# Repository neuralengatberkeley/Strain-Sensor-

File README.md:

# Strain-Sensor-

# ABS Filmanent LM Channels:

3D printed ABS channels to be dissolved in acetone:  

CAD file for 3d prints shown in image above:  ...CAD Files/abs_lofted_insert/basic strain gauge 0p02.ipt

3D printer used -> Original Prusa MK4s

# Strain Sensor Fabrication Procedure:

#  Auto Bender:

All Structural parts (e.g. plates, shaft collars, fasteners) were purchased from goBILDA:  https://www.gobilda.com/

# AutoBender Sensor Circuit:

# AutoBender PCB (which inlcudes sensor circuit and servo circuit):

AutoBender PCB design can be found here in ...Fritzing Files/Voltage Divider PCB/bender PCB.fzz

# Interpreting CSV Data File Columns:

Column A:  Disregard.  It was initially meant to provide the theoretical bend angle, but it is wrong and not used in any calculation.

Column B:  Adafruit BNO055 IMU Pitch Euler Angle (degrees)

Column C:  ADC Value as read from Adafruit Sensor MCP3421 18-Bit ADC (The ADC sensor is in parrallel with the Liquid Metal Strain Gauge (LMSG).  The LMSG is in series 			with a 100 ohm resistor).  Since the code is set to read 14-bits, the possible range of values is from 0 to 2^14 - 1.

Column D:  ADC Value as read from Hall Effect Rotary Encoder (https://p3america.com/erc-series/?srsltid=AfmBOoqSsWeZSXtsMrmoHyB0DRfSCzyFlUfcnEff0gpcv0NyMvrGhVz7).  The 		rotary encoder can rotate from 0 to 320 degrees.  There is a mechanical stop at 0 and 320 degrees.  Since the rotary encoder is connected directly to 			Arduino Uno, the adc output from the Arduino can have values from 0 to 2^10 - 1.  

Note about converting rotary encoder adc value to angle in degrees:  

As a result of this calculation, the rotatry encoder angle should always start at 0 degrees.  The initial IMU angle in degrees typically starts around ~ 3 degrees.  

# Derivation of Change in Resistance Formula as a Function of Axial Strain:

If an axial load is applied to a solid in the x-direction, the solid's lateral dimensions in the y- and z-directions will typically contract, depending on the material properties. The ratio of lateral contraction (negative strain) to axial extension (positive strain) is called Poisson's ratio. The definition includes a negative sign, ensuring that Poisson's ratio is a positive value for materials that contract laterally when stretched axially. 

References:  

1. Soft Robotics Toolkit. (n.d.). Casting soft robots. Retrieved January 14, 2025, 
	from https://softroboticstoolkit.com/book/export/html/206021
2. Craig Jr., R. R. (2011). Mechanics of materials (3rd ed.). Wiley.
3. Hambley, A.R. (2011). Electrical Engineering Principles and Applications (5th ed.).  Prentice Hall.
4. Callister Jr., W. D., & Rethwisch, D. G.  Materials Science and Engineering: An Introduction (10th ed.).  Wiley.
5. Chen, J., Zhang, J., Luo, Z., Zhang, J., Li, L., Su, Y., Gao, X., Li, Y., Tang, W., Cao, C., Liu, Q., Wang, L., & Li, H. (2020). 
	Superelastic, sensitive, and low hysteresis flexible strain sensor based on wave-patterned liquid metal for 
	human activity monitoring. ACS Applied Materials & Interfaces, 12(19), 22200–22211. 
	https://doi.org/10.1021/acsami.0c04709

# Explanation of Model Developed for Axial Strain as a Function of Bend Angle:

The finger joints are modeled as a hinged joint where the leaf rotation axis is concentric with the knuckle axis.  Additionally, the interial surface of the leaf is in contact with the exterior surface of the knuckle.  The change in length of the sample is calculated from the arc length forumla. This model is presented in the image below:

However, in our autobender, the interior rotating surface of the leaf is offset from the exterior surface of the knuckle by an amount delta.  The adjusted AutoBender model is presented in the image below:  

# Expected Trend for Normalized Resistance vs Axial Strain:

The plot below shows theoretical curves of normalized resistance versus axial strain for samples with varying lengths L, but identical liquid metal channel length (Lo) and cross-sectional area (A). The following trends are observed:

1.  As sample length, L, increases (assuming same liquid metal channel lengths and cross-sectional area), the slope of the curve decreases.
2.  A longer sample will experience less axial strain at a 90 degree bend angle
3.  For axial strains below approximately 40% (e.g., in human knuckle models), the relationship can be approximated as linear.
4.  As bend radius (R in this case, not r as indicated in human knuckle model image :/) increases, axial strain also increases for the same bend angle. For example, a strain sensor on a larger knuckle would experience greater axial strain compared to one on a smaller knuckle.  

# "Gluing" LMSG on to fingers:

"paint" Derma-Tac (https://www.smooth-on.com/products/derma-tac/) AND Skin-Tite (https://www.smooth-on.com/products/skin-tite/) onto finger, place sensor on finger for a couple minutes until cross-linking occurs

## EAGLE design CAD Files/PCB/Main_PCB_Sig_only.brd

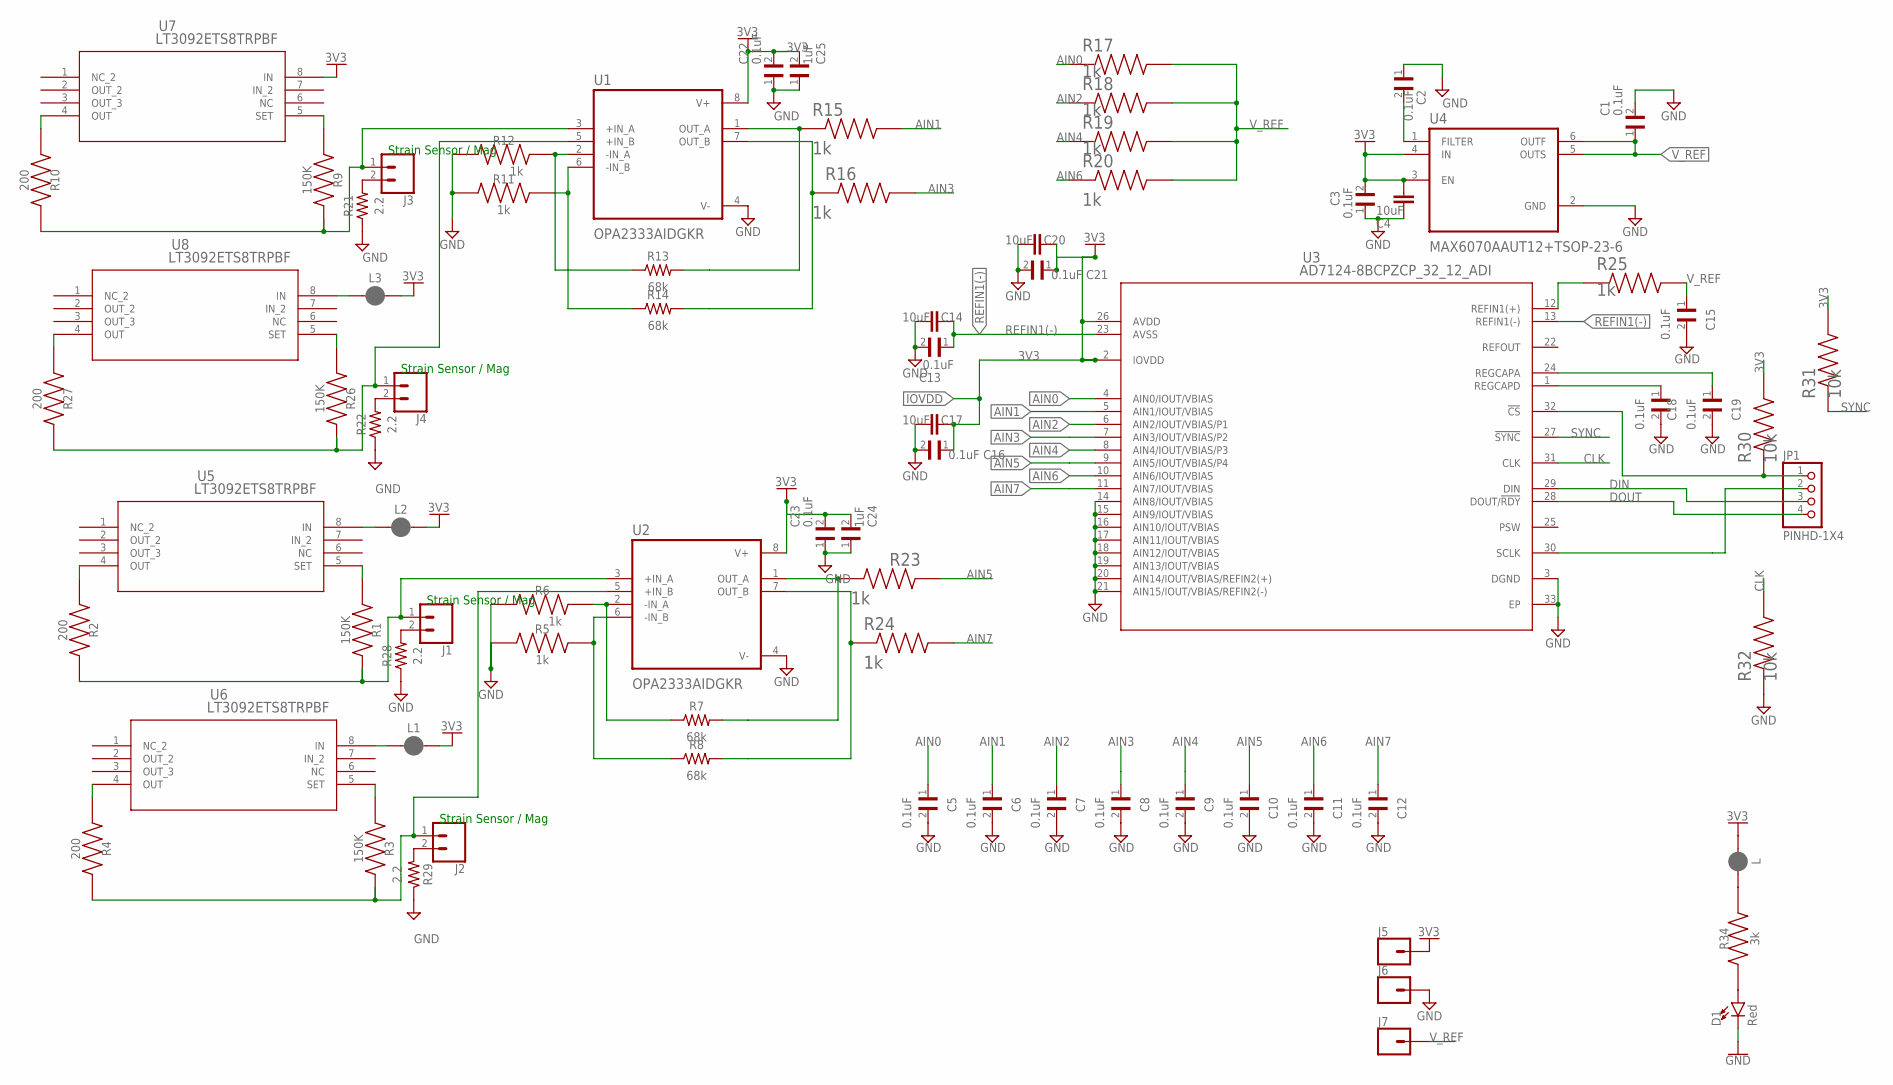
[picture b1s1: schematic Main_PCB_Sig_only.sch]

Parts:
C1, C2, C3, C5, C6, C7, C8, C9, C10, C11, C12, C13, C15, C16, C18, C19, C21, C22, C23: 0.1uF; CAPC0603X33N
C4, C14, C17, C20: 10uF; CAPC1005X60
C24, C25: 1uF; CAPC0603X33N
D1: Red; LED-0603
J1, J2, J3, J4: CONN_02; 1X02
J5, J6, J7: CONN_01PTH_LONGPAD; 1X01_LONGPAD
JP1: PINHD-1X4; 1X04
L, L1, L2, L3: JUMPER-SMT_2_NC_PASTE_NO-SILK; SMT-JUMPER_2_NC_PASTE_NO-SILK
R1, R3, R9, R26: 150K; RESC0603X26N
R2, R4, R10, R27: 200; RESC0603X26N
R5, R6, R11, R12, R15, R16, R17, R18, R19, R20, R23, R24, R25: 1k; RESC0603X26N
R7, R8, R13, R14: 68k; RESC1608X60
R21, R22, R28, R29: 2.2; RESC1608X60
R30, R31, R32: 10k; RESC0603X26N
R34: 3k; RESC0603X26N
U1, U2: OPA2333AIDGKR; SOP65P490X110-8N
U3: AD7124-8BCPZCP_32_12_ADI; CP_32_12_ADI
U4: MAX6070AAUT12+TSOP-23-6; SOT95P280X145-6N
U5, U6, U7, U8: LT3092ETS8TRPBF; TSOT-23_TS8

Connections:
3V3: C3.2, C4.2, C16.1, C17.1, C20.1, C21.1, C22.2, C23.2, C24.2, C25.2, J5.1, L.1, L1.2, L2.2, L3.2, R30.2, R31.2, U1.8 (V+), U2.8 (V+), U3.2 (IOVDD), U3.26 (AVDD), U4.3 (EN), U4.4 (IN), U7.8 (IN)
+IN_A1: J3.1, R9.2, R10.2, U1.3 (+IN_A)
+IN_A2: J1.1, R1.2, R2.2, U2.3 (+IN_A)
+IN_B1: J4.1, R26.2, R27.2, U1.5 (+IN_B)
+IN_B2: J2.1, R3.2, R4.2, U2.5 (+IN_B)
-IN_A1: R12.2, R13.1, U1.2 (-IN_A)
-IN_A2: R6.2, R7.1, U2.2 (-IN_A)
-IN_B1: R11.2, R14.1, U1.6 (-IN_B)
-IN_B2: R5.2, R8.1, U2.6 (-IN_B)
AIN0: C5.1, R17.1, U3.4 (AIN0/IOUT/VBIAS)
AIN1: C6.1, R15.2, U3.5 (AIN1/IOUT/VBIAS)
AIN2: C7.1, R18.1, U3.6 (AIN2/IOUT/VBIAS/P1)
AIN3: C8.1, R16.2, U3.7 (AIN3/IOUT/VBIAS/P2)
AIN4: C9.1, R19.1, U3.8 (AIN4/IOUT/VBIAS/P3)
AIN5: C10.1, R23.2, U3.9 (AIN5/IOUT/VBIAS/P4)
AIN6: C11.1, R20.1, U3.10 (AIN6/IOUT/VBIAS)
AIN7: C12.1, R24.2, U3.11 (AIN7/IOUT/VBIAS)
CLK: R32.2, U3.31 (CLK)
CS: JP1.1, R30.1, U3.32 (!CS)
DIN: JP1.3, U3.29 (DIN)
DOUT: JP1.4, U3.28 (DOUT/!RDY)
GND: C1.2, C2.1, C3.1, C4.1, C5.2, C6.2, C7.2, C8.2, C9.2, C10.2, C11.2, C12.2, C13.2, C14.2, C15.2, C16.2, C17.2, C18.2, C19.2, C20.2, C21.2, C22.1, C23.1, C24.1, C25.1, D1.C, J6.1, R5.1, R6.1, R11.1, R12.1, R21.1, R22.1, R28.1, R29.1, R32.1, U1.4 (V-), U2.4 (V-), U3.3 (DGND), U3.14 (AIN8/IOUT/VBIAS), U3.15 (AIN9/IOUT/VBIAS), U3.16 (AIN10/IOUT/VBIAS), U3.17 (AIN11/IOUT/VBIAS), U3.18 (AIN12/IOUT/VBIAS), U3.19 (AIN13/IOUT/VBIAS), U3.20 (AIN14/IOUT/VBIAS/REFIN2(+)), U3.21 (AIN15/IOUT/VBIAS/REFIN2(-)), U3.33 (EP), U4.2 (GND)
I_OUT1: R10.1, U7.4 (OUT)
I_OUT2: R27.1, U8.4 (OUT)
I_OUT3: R2.1, U5.4 (OUT)
I_OUT4: R4.1, U6.4 (OUT)
I_SET1: R9.1, U7.5 (SET)
I_SET2: R26.1, U8.5 (SET)
I_SET3: R1.1, U5.5 (SET)
I_SET4: R3.1, U6.5 (SET)
unnamed: L1.1, U6.8 (IN)
unnamed: C2.2, U4.1 (FILTER)
unnamed: J3.2, R21.2
unnamed: J4.2, R22.2
unnamed: J1.2, R28.2
unnamed: J2.2, R29.2
unnamed: L.2, R34.2
unnamed: D1.A, R34.1
unnamed: L2.1, U5.8 (IN)
unnamed: L3.1, U8.8 (IN)
OUT_A1: R13.2, R15.1, U1.1 (OUT_A)
OUT_A2: R7.2, R23.1, U2.1 (OUT_A)
OUT_B1: R14.2, R16.1, U1.7 (OUT_B)
OUT_B2: R8.2, R24.1, U2.7 (OUT_B)
REFIN1(+): R25.1, U3.12 (REFIN1(+))
REFIN1(-): C13.1, C14.1, U3.13 (REFIN1(-)), U3.23 (AVSS)
REGCAPA: C19.1, U3.24 (REGCAPA)
REGCAPD: C18.1, U3.1 (REGCAPD)
SCLK: JP1.2, U3.30 (SCLK)
SYNC: R31.1, U3.27 (!SYNC)
V_REF: C1.1, C15.1, J7.1, R17.2, R18.2, R19.2, R20.2, R25.2, U4.5 (OUTS), U4.6 (OUTF)

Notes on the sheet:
Strain Sensor / Mag

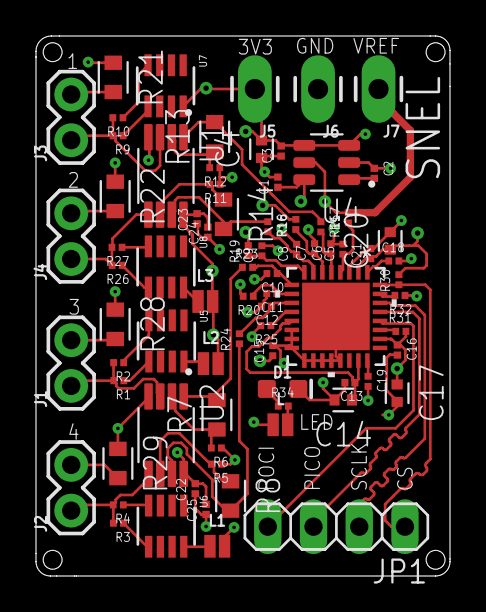
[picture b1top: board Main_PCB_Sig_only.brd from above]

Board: 4 copper layers, 23.0 x 30.0 mm, 79 parts (0 on the bottom side), 51 nets.

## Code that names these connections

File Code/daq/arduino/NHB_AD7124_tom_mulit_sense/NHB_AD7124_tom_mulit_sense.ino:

#include <NHB_AD7124.h>

#define CH_COUNT 4  // 4 differential pairs (AIN0–1, AIN2–3, AIN4–5, AIN6–7)

// Buffer for ADC readings
double buf[CH_COUNT];
const uint8_t csPin = 5;
double exRefV = 2.048;
AD7124_BurnoutCurrents burnout;
Ad7124 adc(csPin, 4000000);  // SPI @ 4 MHz

#define CONVMODE AD7124_OpMode_Continuous  // Continuous conversion mode
int filterSelBits = 100;  // Adjust this based on noise/speed tradeoff

void setup() {
  Serial.begin(115200);
  while (!Serial) {
    ;  // Wait for Serial to be ready
  }

  Serial.println("AD7124 - 4 Differential Channel Read Example");

  // Initialize ADC
  adc.begin();

  // Set mode and power
  adc.setAdcControl(CONVMODE, AD7124_FullPower, true);  // true = enable reference

  // Configure Setup 4:
  // - External reference (e.g., 3.3V)
  // - Gain = 32 → ±103 mV input range
  // - Bipolar mode (true)
  adc.setup[0].setConfig(AD7124_Ref_ExtRef1, AD7124_Gain_32, true, burnout, exRefV);
  adc.setup[0].setFilter(AD7124_Filter_SINC3, filterSelBits);
  adc.setup[1].setConfig(AD7124_Ref_ExtRef1, AD7124_Gain_32, true, burnout, exRefV);
  adc.setup[1].setFilter(AD7124_Filter_SINC3, filterSelBits);
  adc.setup[2].setConfig(AD7124_Ref_ExtRef1, AD7124_Gain_32, true, burnout, exRefV);
  adc.setup[2].setFilter(AD7124_Filter_SINC3, filterSelBits);
  adc.setup[3].setConfig(AD7124_Ref_ExtRef1, AD7124_Gain_32, true, burnout, exRefV);
  adc.setup[3].setFilter(AD7124_Filter_SINC3, filterSelBits);

  // Enable 4 fully differential input channels using Setup 4
  adc.setChannel(0, 0, AD7124_Input_AIN4, AD7124_Input_AVSS, true);  // CH0
  adc.setChannel(1, 1, AD7124_Input_AIN1, AD7124_Input_AVSS, true);  // CH1
  adc.setChannel(2, 2, AD7124_Input_AIN2, AD7124_Input_AVSS, true);  // CH2
  adc.setChannel(3, 3, AD7124_Input_AIN3, AD7124_Input_AVSS, true);  // CH3
}

void loop() {
  const int activeChannels[CH_COUNT] = {0, 1, 2, 3};  // Channel indices in ADC

  for (int i = 0; i < CH_COUNT; i++) {
    buf[i] = adc.readVolts(activeChannels[i]);  // Read differential voltage
    Serial.print(buf[i], 6);
    Serial.print("\t");
  }

  Serial.println();
  delay(6);  // Adjust for sampling rate / readability
}

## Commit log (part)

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2024-10-29 Added CAD and Blender Files
    Added CAD and Blender Files
2024-11-04 CAD Files Added
    CAD Files Added
2024-11-14 Phil Code Add
    Phil Code Add
2024-11-14 Added single loop strain abs sensor
    Added single loop strain abs sensor
2024-11-14 added files
2024-12-12 New Files
    New Files
2024-12-18 new servo code
2024-12-18 Code and Data Added
2024-12-19 new code and data
2024-12-19 updated presentation from 12/19/24
2025-01-07 Consolidated Files and Folders
    Consolidated Files and Folders
2025-01-09 added code
2025-01-13 Organized CAD folders and added images
2025-01-13 added analysis and daq folder and files
2025-01-14 Added Folders
2025-01-14 added angle testing image
2025-01-15 added to read me
2025-01-16 added images to read me
2025-01-16 adding xls sheet download to keep paired with the repo
2025-01-16 ipynb with examples of new refactored analysis.py code
2025-01-16 preeya updates during 1/15/25 code review -- cleaning up load_data method, refactoring plotting / accuracy, adding data scatter for visualizing temporal changes
2025-01-16 config file with path info
2025-01-21 added to analysis
2025-01-22 added to bender class and analysis code
2025-01-22 changed master csv file
2025-01-22 added kinematic presentation folder
2025-01-23 updated analysis files
2025-01-23 Updated Code
2025-01-23 updated analysis code
2025-01-24 added DS_all and errorbars to Toms plot
2025-01-24 added old Bender class so toms old code is still runnable
2025-01-24 Updated analysis comparison
2025-02-04 new reapplication data
2025-02-06 new reapplication data and analysis
2025-02-11 Sensor Fab and Mis Data
    Collected new misalignment data on two additional samples. Also created cad files and png image for sensor fabrication image for future paper
2025-02-13 added bender_class methods
2025-02-18 updated bender_class and added analysis code
    updated bender_class , added analysis code, and created prelim fig 1
2025-02-27 updated error analysis
2025-02-27 updated analysis
2025-03-05 added CAD files, analysis, and fig 1
2025-03-08 updates fab image renderings
2025-03-13 added fig 1 images
2025-03-14 minor changes/comments. Only main change was moving self.all_accuracies out of the itneration loop
2025-03-14 add notebook that checks erorr analysis.ipynb
2025-03-14 added new tab for PK data check of fig 1
2025-03-14 saved notebook
2025-03-17 preeya reconstruction of fig 1 plots
2025-03-17 added absolute error metrics to places where model is trained and tested so dont need specific fcns to do this
2025-03-17 general cleanup
2025-03-17 ensured entirety of test data is evaluated, added analysis to get min_angle_100 for each iteration, and added method to plot mean and std of list as part of plotting bars
2025-03-17 data updates to PK tab
2025-03-17 updates to PK ipynb
2025-03-18 changed some csv file names and made sure Preeya code worked on my end
    corrected some csv file names to consistent with rest of filenames.
2025-03-18 conducted ~ 10 retests wtih 16 ADC and 8x amp
2025-03-20 New voltage divider circuit and retests
2025-04-09 added data, daq code, and modified analysis
    added data, daq code, and modified analysis delta norm to take into account negative and pos adc values
2025-04-09 updated 4_9_25 presentation
2025-04-11 Python DAQ, new CSV files, and Analsys.py change
    Added a GUI to the python daq so that user can enter sample info. Also, csv auto saved in correct folder. Changed analysis accuracy method so that instead in incremeting angle of min accuracy by 1, i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
2025-04-15 Acquired More Data, Changed analysis.py to include quadratic fitting
2025-04-18 1 sample of reapplicaton and misalignment with Velcro...updated presentation
2025-04-18 collected reapplication and misalignment data with velcro
2025-04-22 finished testing misalignment, reapplication, and length data. All code updated
2025-04-25 updated circuit
2025-04-29 improved organization of datafile,
2025-04-30 Updated data spreadsheet and reapplication analysis code
2025-04-30 updated datasheet for clarity one last time
2025-05-05 new data acquired and new arduino daq
2025-05-12 new data
2025-05-14 circuit design for camera setup and new reapp analysis
2025-05-23 new data acquired for model testing
2025-06-06 new data and data vs model analysis
2025-06-06 updated model analysis notebook
2025-06-06 updated model fitting analysis
2025-06-12 added arduino code for mcp3564 adc
2025-06-13 updated adc code for MCP3564
2025-07-02 new ad7124 arduino code and stereo cam code
2025-07-18 new camera, DAQ, and adc code!
2025-08-13 added camera analysis code
2025-08-13 new dlc class methods
2025-08-14 completed camera_encoder_cal code
2025-08-14 completed camera_encoder_cal notebook
2025-08-15 updated figures
2025-08-18 updated figures and analysis code
2025-08-22 updated analysis.py and camera jupyter notebook
2025-08-25 modified camera notebook
2025-08-27 code to analyze mediapipe data
2025-08-29 added MediaPipe and HaMeR code
2025-09-02 MATLAB calibration worked
2025-09-05 strain vs encoder code
    added notebook code for calibration of strain sensor on autobender using rpi breakout board
2025-09-10 more changes
2025-09-16 added BallBearingData Class for notebook
2025-09-21 wrote code for tom marble analysis
2025-09-21 tom marble updated
2025-09-22 updated tom marble analysis
2025-09-23 updated tom marble notebook
2025-09-23 updated csv folder for Phil
2025-09-29 added signed angle calc, angle error calc, summary image
2025-09-29 added signed option for angle_from_vectors()
2025-09-29 added sign/unsigned knob
2025-09-29 updated analysis.py and tom marble
2025-09-29 updated analysis.py, matched timestamps
2025-10-01 updated analysis and notebooks
2025-10-01 added signed option to angle calc function
2025-10-01 updated tom_marble notebook
2025-10-01 analysis and tom marble updated
2025-10-01 updated analysis and tom_marble
2025-10-01 updated analysis.py
2025-10-02 Phil changes before lab mtg pres
2025-10-08 updated analysis and tom marble notebook
2025-10-09 angle comparisons between DLC 3D
2025-10-09 signed angles_from_vectors func
2025-11-04 updates
    1. updates to fig 1
    2. updates to analysis.py
    3. updates to tom_marble notebook code
2025-11-10 updates to analysis
2025-11-11 updated analysis and adc and imu plotting
2025-11-11 added imu_ciode for plotting
2025-11-12 updated imu and tom marble code.
2025-11-13 created new ADC_CAM class and ADC am notebook
2025-11-14 adc error analysis complete
2025-11-15 adc analysis updated
2025-11-15 updated adc_vs_cam notebook
2025-11-17 updated adc_cam analysis
2025-11-25 updated adc and imu classes and notebooks
2025-11-25 created method for paper fig error bars
2025-11-25 summary plots updated
2025-11-26 created single code for fig 1 nice
2025-11-26 updated fig 1
2025-12-02 updated imu figure code
2025-12-02 updated code for adc cam figure
2025-12-03 added calibration plot to fig 2
2025-12-03 updated code for plotting figure 2
2025-12-08 fig 1 iteration
2025-12-09 fig 2 iteration
2025-12-09 fig 3 iteration
2025-12-11 fig 2 and 3 iteration
2025-12-11 fig 2 suppress warnings
2025-12-12 fig 2 iteration and p4 supp figure made
2026-01-28 figure label iterations
2026-01-28 fig iter
2026-01-29 more code, updated circuits
2026-01-29 new code and circuits diagrams
2026-01-29 reloaded checkpoint files
2026-01-29 fig2 new
2026-01-29 IMU_vs_cam notebook
2026-02-03 added abduction anal code and rename abd csv file name
2026-02-06 ignore
2026-02-09 .ds -ignore
2026-02-09 supp fig made -ignore
2026-03-02 updated Fig 4 plot and imu analysis
2026-03-02 updated imu_vs_cam analysis and fig code
2026-03-02 fig 4 update
2026-03-06 plotted timestamp on x axis in sec
    legend displays correct total elapsed time
2026-03-06 correct time from timestamps plotted
2026-03-09 add .gitignore
2026-03-09 Ignore Python cache files and .DS_Store
2026-03-09 adding global gitignore
2026-03-09 added long term analysis code
2026-03-09 gitignore long_term_wear_data
2026-03-09 flex/ext from long term wear
2026-03-09 naive ADC -> degree
2026-03-10 adding ad_ab analysis
2026-03-16 gitignore update
2026-04-03 added content to adc code
2026-04-17 long wear figs
2026-04-27 long plot updates
2026-04-27 upload ad/ab file
2026-05-01 ad_ab supp figure updates
2026-06-16 Add user comfort analysis folder
2026-06-16 Update wear analysis plots and data
2026-06-16 Ignore macOS system files
2026-06-16 Ignore large raw wear data files

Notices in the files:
parts and their libraries:
SparkFun-LED: Licensing: Creative Commons ShareAlike 4.0 International - https://creativecommons.org/licenses/by-sa/4.0
COPYRIGHT: Copyright (C) 2025 Ultra Librarian. All rights reserved.
